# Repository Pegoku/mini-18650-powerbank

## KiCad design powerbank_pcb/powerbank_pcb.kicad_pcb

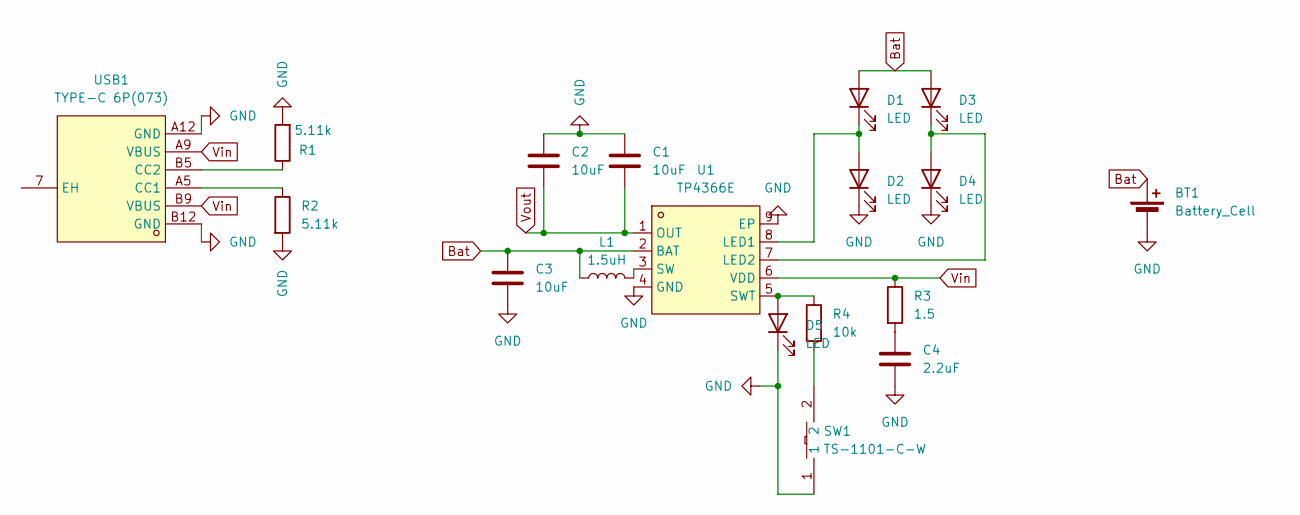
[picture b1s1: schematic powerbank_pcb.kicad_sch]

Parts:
BT1: Battery_Cell; PinHeader_1x02_P2.54mm_Horizontal
C1, C2, C3: 10uF; C_1206_3216Metric
C4: 2.2uF; C_1206_3216Metric
D1, D2, D3, D4, D5: LED; LED_0201_0603Metric; LCSC C965807
L1: 1.5uH; IND-SMD_L7.2-W6.6_GPSR0730; LCSC C5189745
R1, R2: 5.11k; R_1206_3216Metric
R3: 1.5; R_1206_3216Metric
R4: 10k; R_1206_3216Metric
SW1: TS-1101-C-W; SW-SMD_L6.0-W3.3-LS8.0; LCSC Part C318938
U1: TP4366E; ESOP-8_L4.9-W3.9-P1.27-LS6.0-BL-EP; LCSC Part C382127
USB1: TYPE-C 6P(073); TYPE-C-SMD_TYPE-C-6P_5; LCSC Part C668623

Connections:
Bat: BT1.1 (+), C3.1, D1.2 (A), D3.2 (A), L1.1, U1.2 (BAT)
GND: BT1.2 (-), C1.1, C2.1, C3.2, C4.2, D2.1 (K), D4.1 (K), D5.1 (K), R1.2, R2.2, SW1.1, U1.4 (GND), U1.9 (EP), USB1.A12 (GND), USB1.B12 (GND)
unnamed: C4.1, R3.2
unnamed: D1.1 (K), D2.2 (A), U1.8 (LED1)
unnamed: D3.1 (K), D4.2 (A), U1.7 (LED2)
unnamed: D5.2 (A), R4.1, U1.5 (SWT)
unnamed: R4.2, SW1.2
unnamed: L1.2, U1.3 (SW)
unnamed: R2.1, USB1.A5 (CC1)
unnamed: R1.1, USB1.B5 (CC2)
Vin: R3.1, U1.6 (VDD), USB1.A9 (VBUS), USB1.B9 (VBUS)
Vout: C1.2, C2.2, U1.1 (OUT)

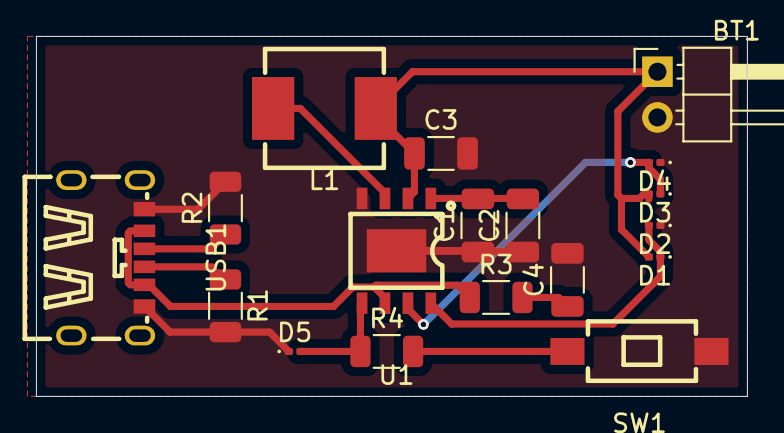
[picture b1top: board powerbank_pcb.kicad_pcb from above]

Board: 2 copper layers, 39.5 x 20.0 mm, 18 parts (0 on the bottom side), 12 nets.

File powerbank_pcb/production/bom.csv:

Designator,Footprint,Quantity,Value,LCSC Part #
BT1,PinHeader_1x02_P2.54mm_Horizontal,1,Battery_Cell,
"C1, C2, C3",1206,3,10uF,
C4,1206,1,2.2uF,
"D1, D2, D3, D4, D5",0201,5,LED,C965807
L1,IND-SMD_L7.2-W6.6_GPSR0730,1,1.5uH,C5189745
"R1, R2",1206,2,5.11k,
R3,1206,1,1.5,
R4,1206,1,10k,
SW1,SW-SMD_L6.0-W3.3-LS8.0,1,TS-1101-C-W,C318938
U1,ESOP-8_L4.9-W3.9-P1.27-LS6.0-BL-EP,1,TP4366E,C382127
USB1,TYPE-C-SMD_TYPE-C-6P_5,1,TYPE-C 6P(073),C668623

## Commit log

2024-08-23 start
